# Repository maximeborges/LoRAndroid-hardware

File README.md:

# LoRAndroid-hardware
Hardware source files for LoRAndroid project

## Get my symbols, footprints and 3D packages

Since not all my symbols, footprints and 3D package have been merged into the official repos yet, here are my forks that follows the `master` of each official repo (synces every hours using Github `Pull` app).

Symbols: https://github.com/maximeborges/kicad-symbols
Footprints: https://github.com/maximeborges/kicad-footprints
3D Packages: https://github.com/maximeborges/kicad-packages3D

You can add my repositories as remotes and check them out using the following comands: 

    cd kicad-symbols &&
    git remote add maximeborges git@github.com:maximeborges/kicad-symbols &&
    git checkout maximeborges/master -b maximeborges-master &&
    cd ..
    cd kicad-footprints &&
    git remote add maximeborges git@github.com:maximeborges/kicad-footprints &&
    git checkout maximeborges/master -b maximeborges-master &&
    cd ..
    cd kicad-packages3d &&
    git remote add maximeborges git@github.com:maximeborges/kicad-packages3d &&
    git checkout maximeborges/master -b maximeborges-master &&
    cd ..
    
To get back to the official repos and cleanup everything, you can use the following commands:

    cd kicad-symbols &&
    git branch -d maximeborges-master &&
    git remote rm maximeborges &&
    cd ..
    cd kicad-footprints &&
    git branch -d maximeborges-master &&
    git remote rm maximeborges &&
    cd ..
    cd kicad-packages3d &&
    git branch -d maximeborges-master &&
    git remote rm maximeborges &&
    cd ..

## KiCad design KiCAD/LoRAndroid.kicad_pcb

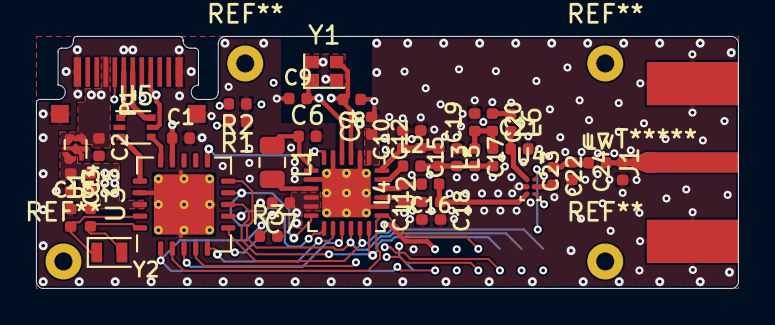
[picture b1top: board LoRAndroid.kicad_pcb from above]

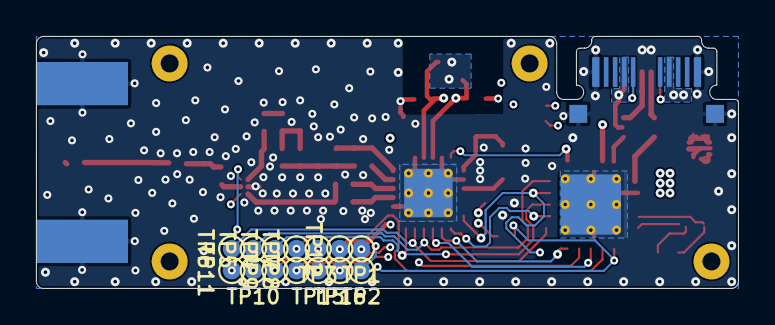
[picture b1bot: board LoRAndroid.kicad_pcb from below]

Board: 4 copper layers, 39.0 x 14.0 mm, 58 parts (14 on the bottom side), 39 nets.

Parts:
C1, C6: 470n; C_0402_1005Metric
C2, C3, C4: 1u; C_0402_1005Metric
C5, C7: 100n; C_0402_1005Metric
C8, C9, C13, C14: 33pF; C_0402_1005Metric
C10: 47p; C_0402_1005Metric
C11: 1.8p; C_0402_1005Metric
C12: 47n; C_0402_1005Metric
C15, C18, C23, C24: DNP; C_0402_1005Metric
C16: 2.4p; C_0402_1005Metric
C17: 3.3p; C_0402_1005Metric
C19: 5.6p; C_0402_1005Metric
C20, C22: 39p; C_0402_1005Metric
C21: 2.2p; C_0402_1005Metric
J1: SMA; SMA_Cinch_142-0701-881_EdgeMount
L1: 15u; L_0805_2012Metric
L2, L7: 0R; L_0402_1005Metric
L3: 47n; L_0402_1005Metric
L4: 15n; L_0402_1005Metric
L5: 2.5n; L_0402_1005Metric
L6: 4.7n; L_0402_1005Metric
P1: DX07P022AA6; USB_C_Plug_JAE_DX07P022AA6
R1, R2: 5.1k; R_0402_1005Metric
R3: 1-10k; R_0402_1005Metric
TP1, TP2, TP3, TP4, TP5, TP6, TP7, TP8, TP9, TP10, TP11, TP12, TP15, TP16: TestPoint; TestPoint_Pad_D1.0mm_NoCourtyard
U1: MIC5504-3.3YMT; Microchip_DFN-4-1EP_1x1mm_P0.65mm_EP0.48x0.48mm
U2: SX1262; QFN-24-1EP_4x4mm_P0.5mm_EP2.7x2.7mm_ThermalVias
U3: MCP2210-I-MQ; QFN-20-1EP_5x5mm_P0.65mm_EP3.35x3.35mm_ThermalVias
U4: BGS12SN6; TSNP-6-2_1.1x0.7mm_P0.4mm
U5: USBLC6-2P6; SOT-666
Y1: XRCGB32M000FBH50R0; Crystal_SMD_Murata_HCR2016-4Pin_2.0x1.6mm
Y2: CSTCE12M0G15L; Crystal_SMD_2012-2Pin_2.0x1.2mm
uwT*****: uwT0.00_0.30_0.50_1.14_1.25

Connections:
+3V3: C1.1, C3.1, C4.1, C5.1, C7.1, R3.2, TP12.1, U1.1, U2.1, U2.10, U2.11, U3.14, U3.18, U4.4
/BUSY: TP8.1, U2.14, U3.5
/CS: TP7.1, U2.19, U3.2
/D+: U3.16, U5.3
/D-: U3.15, U5.4
/DIO1: TP9.1, U2.13, U3.7
/DIO2: TP10.1, U2.12, U3.9
/DIO3: TP11.1, U2.6, U3.11
/MISO: TP5.1, U2.16, U3.10
/MOSI: TP6.1, U2.17, U3.6
/SCK: TP4.1, U2.18, U3.8
/SPI_~RST: R3.1, TP16.1, U3.1
/SX_~RST: TP3.1, U2.15, U3.3
/TX_~RX: TP15.1, U3.4, U4.6
/VREG: C6.1, L1.1, U2.7
/V_USB: C2.1, P1.A4, P1.A9, P1.B4, P1.B9, TP2.1, U1.3, U1.4, U5.5
GND: C1.2, C2.2, C3.2, C4.2, C5.2, C6.2, C7.2, C8.1, C9.1, C10.2, C11.1, C12.2, C13.1, C14.1, C15.2, C18.2, C19.2, C21.2, C23.1, C24.1, J1.2, P1.A1, P1.A12, P1.B1, P1.B12, P1.S1, R1.1, R2.1, TP1.1, U1.2, U1.5, U2.2, U2.5, U2.8, U2.20, U2.25, U3.17, U3.21, U4.2, U5.2
unnamed: C8.2, U2.3, Y1.3
unnamed: C9.2, U2.4, Y1.1
unnamed: C10.1, C12.1, L3.1, U2.24
unnamed: C11.2, L4.1, U2.21
unnamed: C13.2, U3.19, Y2.1
unnamed: C14.2, U3.20, Y2.2
unnamed: C15.1, C17.2, L2.2, L3.2, L5.1
unnamed: C16.1, C18.1, U4.3
unnamed: C16.2, L4.2, U2.22
unnamed: C17.1, C19.1, C20.2, L5.2
unnamed: C20.1, L6.1
unnamed: C21.1, L6.2, U4.1
unnamed: C22.1, C23.2, L7.1
unnamed: C22.2, U4.5
unnamed: C24.2, J1.1, L7.2, uwT*****.1
unnamed: L1.2, U2.9
unnamed: L2.1, U2.23
unnamed: P1.A5, R1.2
unnamed: P1.A6, U5.1
unnamed: P1.A7, U5.6
unnamed: P1.B5, R2.2
unnamed: Y1.2, Y1.4

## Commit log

2019-10-05 revA
2019-10-05 Add SVG plto of schematics and board layout
2019-10-05 Add images in README
2019-10-07 Review, add TVS and mounting holes
2019-11-26 Update SMA, add POR resistor for MCP2210, small fixes
2019-12-09 Update images and README
